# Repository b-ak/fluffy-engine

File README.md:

## fluffy-engine 
  Informal experiments from home

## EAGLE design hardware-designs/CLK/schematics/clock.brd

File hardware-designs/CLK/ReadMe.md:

## Clock

A clock using Four, 1 inch 7 segment displays and One Shift register. Runs with an arduino Nano. 
Powered by a 5V adapter and USB Mini B cable. Uses a DS3231 RTC. 

[Credits to korolg for the Idea and Code](http://fritzing.org/projects/7-segment-led-clock-with-multiplexing)

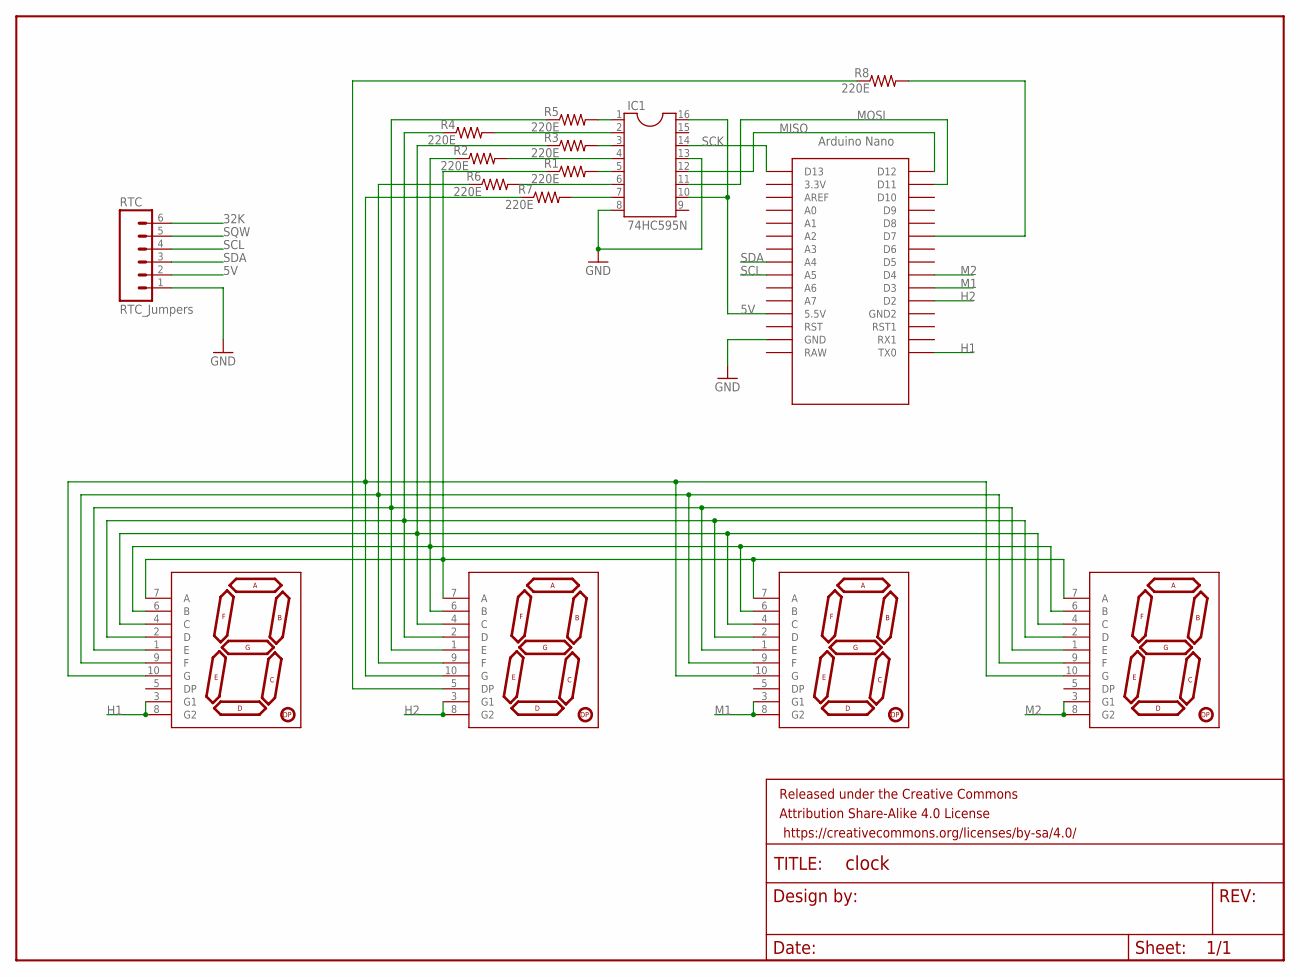
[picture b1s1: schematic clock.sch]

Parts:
FRAME1: FRAME-LETTERNO_PACKAGE; DUMMY
IC1: 74HC595N; DIL16
R1, R2, R3, R4, R5, R6, R7, R8: 220E; 0309/10
RTC: RTC_Jumpers; 1X06
U$1, U$2, U$3, U$4: 7-SEGMENT-1INCH-DIGIT-RED; 7-SEGMENT-1"PTH
U$5: NANO

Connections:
5V: IC1.10, IC1.16, RTC.2, U$5.5V (5.5V)
32K: RTC.6
A: R1.1, U$1.7 (A), U$2.7 (A), U$3.7 (A), U$4.7 (A)
B: R2.1, U$1.6 (B), U$2.6 (B), U$3.6 (B), U$4.6 (B)
C: R3.1, U$1.4 (C), U$2.4 (C), U$3.4 (C), U$4.4 (C)
D: R4.1, U$1.2 (D), U$2.2 (D), U$3.2 (D), U$4.2 (D)
D7: R8.2, U$5.D7
DP: R8.1, U$2.5 (DP)
E: R5.1, U$1.1 (E), U$2.1 (E), U$3.1 (E), U$4.1 (E)
F: R6.1, U$1.9 (F), U$2.9 (F), U$3.9 (F), U$4.9 (F)
G: R7.1, U$1.10 (G), U$2.10 (G), U$3.10 (G), U$4.10 (G)
GND: IC1.8, IC1.13, RTC.1, U$5.GND
H1: U$1.3 (G1), U$1.8 (G2), U$5.TX0
H2: U$2.3 (G1), U$2.8 (G2), U$5.D2
M1: U$3.3 (G1), U$3.8 (G2), U$5.D3
M2: U$4.3 (G1), U$4.8 (G2), U$5.D4
MISO: IC1.12, U$5.D12
MOSI: IC1.11, U$5.D11
Q1: IC1.1, R5.2
Q2: IC1.2, R4.2
Q3: IC1.3, R3.2
Q4: IC1.4, R2.2
Q5: IC1.5, R1.2
Q6: IC1.6, R6.2
Q7: IC1.7, R7.2
SCK: IC1.14, U$5.D13
SCL: RTC.4, U$5.A5
SDA: RTC.3, U$5.A4
SQW: RTC.5

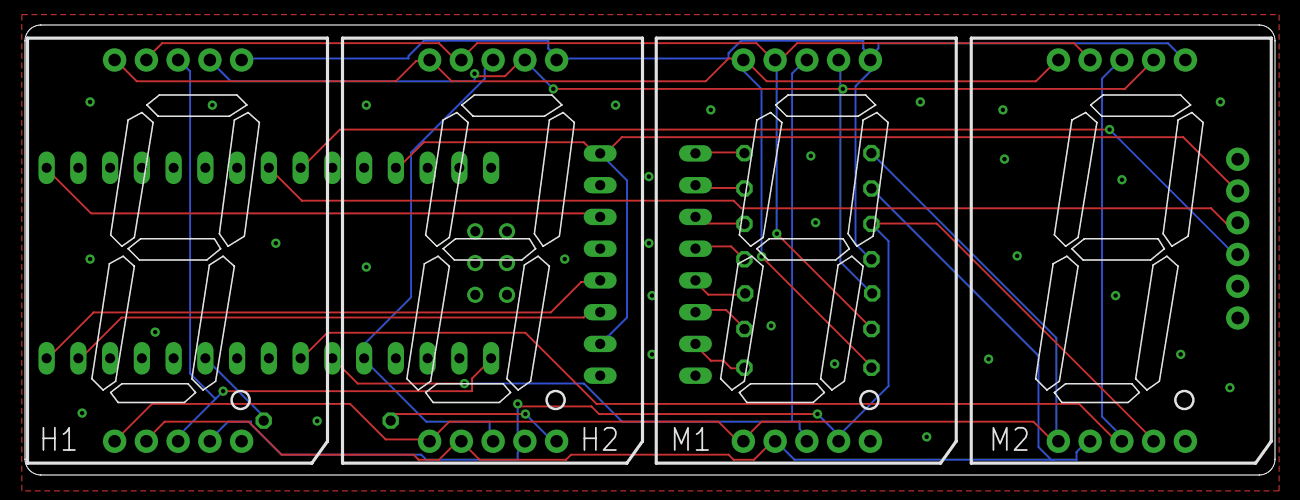
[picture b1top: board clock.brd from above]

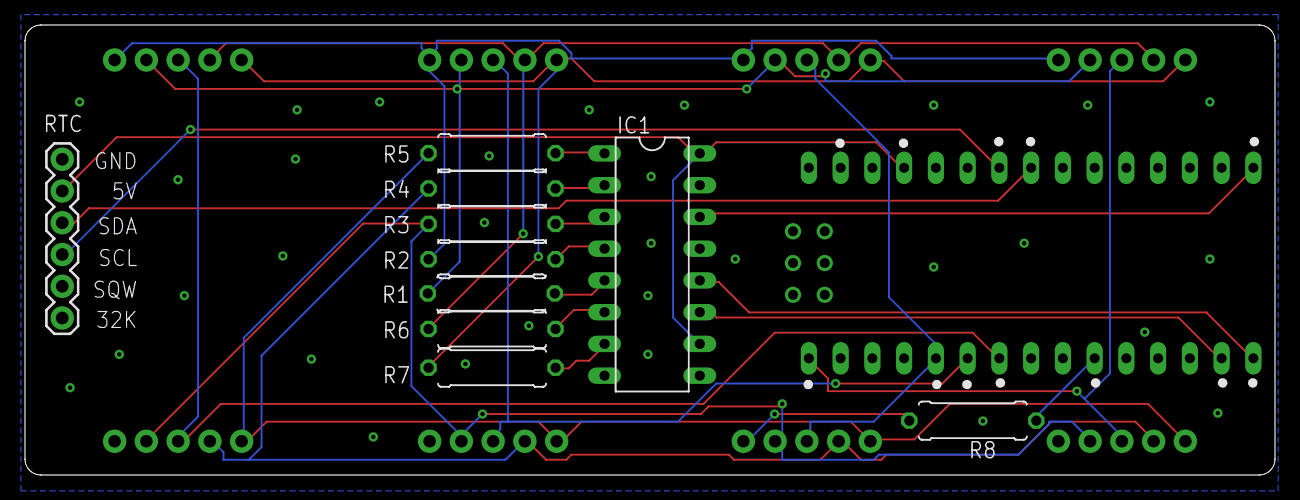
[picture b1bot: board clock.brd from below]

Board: 2 copper layers, 100.0 x 36.0 mm, 16 parts (11 on the bottom side), 27 nets.

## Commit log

2019-01-23 Lots of raspberrypi data
2019-01-23 Hardware projects and eagle files/libraries
2019-01-23 Updated files
2019-01-31 Added files
2020-07-21 bash-it files and how-to
2021-02-09 Add files via upload
    Moving gists to this repo
2021-09-29 [RPi] - Added new directory
2021-09-29 [Helper-Scripts] - Added all scripts into single repo
2021-09-29 [Hardware Designs] - Adding all harware designs
2021-09-29 [py] - Added all python files
2021-10-04 [ReadMe] - Added a readme file
2021-10-19 Update cmd_cheatsheet
2022-02-07 Android 11(Omnirom) on RPi-4
2022-03-03 Mic Record
2022-03-03 Wave FIle Analyser
2022-04-18 Updates to bash-it setup
2022-04-21 Converting Markdown to Jupyter Notebook

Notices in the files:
parts and their libraries:
SparkFun-Connectors: Licensing: CC v3.0 Share-Alike You are welcome to use this library for commercial purposes.
SparkFun-Aesthetics: Released under the Creative Commons Attribution Share-Alike 4.0 License
SparkFun-Aesthetics: https://creativecommons.org/licenses/by-sa/4.0
